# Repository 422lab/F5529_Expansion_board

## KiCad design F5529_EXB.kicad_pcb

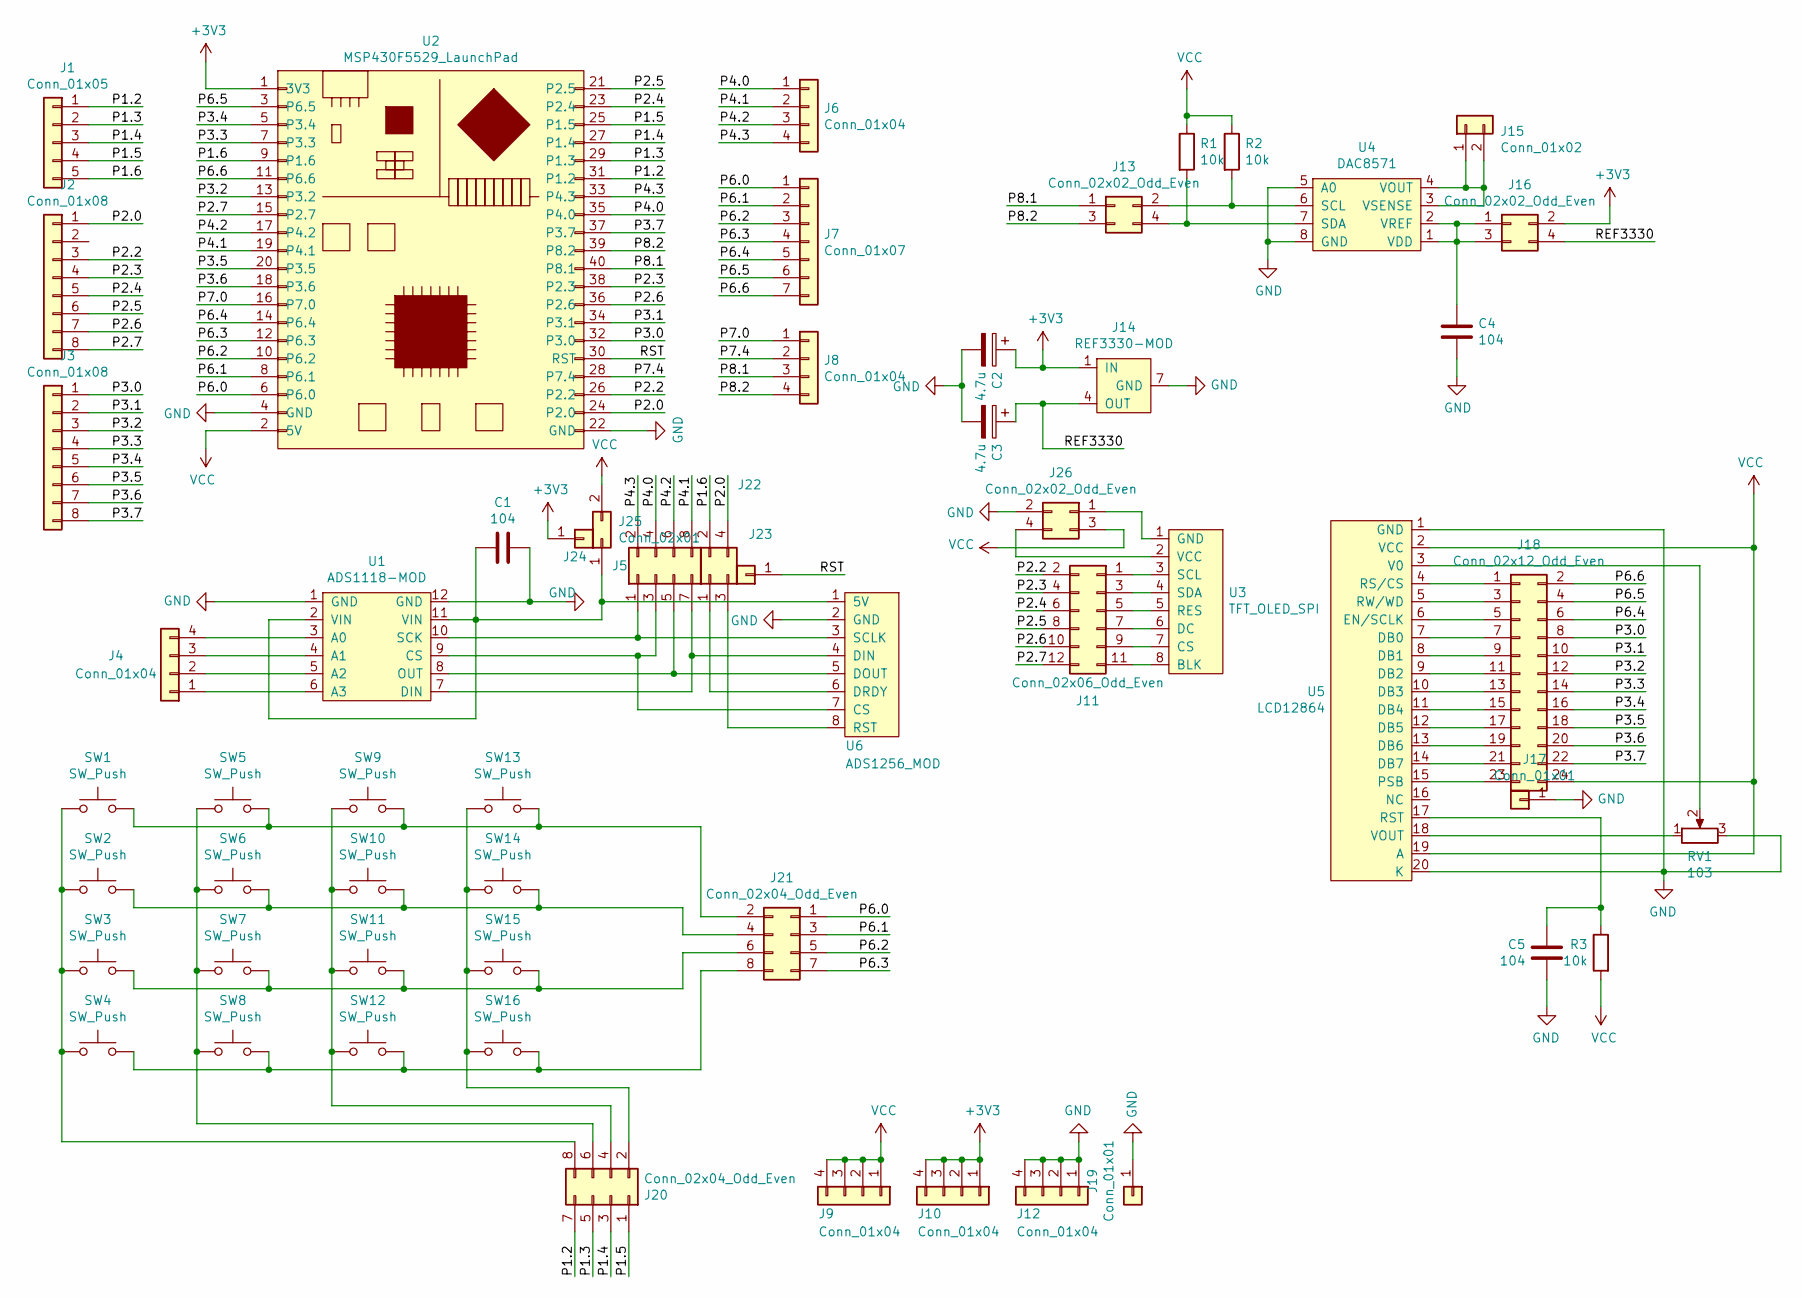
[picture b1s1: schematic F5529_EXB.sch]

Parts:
C1, C4, C5: 104; C_Disc_D3.0mm_W1.6mm_P2.50mm
C2, C3: 4.7u; CP_Radial_D5.0mm_P2.50mm
J1: Conn_01x05; PinHeader_1x05_P2.54mm_Vertical
J2, J3: Conn_01x08; PinHeader_1x08_P2.54mm_Vertical
J4, J6, J8, J9, J10, J12: Conn_01x04; PinHeader_1x04_P2.54mm_Vertical
J5, J20, J21: Conn_02x04_Odd_Even; PinHeader_2x04_P2.54mm_Vertical
J7: Conn_01x07; PinHeader_1x07_P2.54mm_Vertical
J11: Conn_02x06_Odd_Even; PinHeader_2x06_P2.54mm_Vertical
J13, J16, J22, J26: Conn_02x02_Odd_Even; PinHeader_2x02_P2.54mm_Vertical
J14: REF3330-MOD; DIP-8_W7.62mm
J15: Conn_01x02; PinHeader_1x02_P2.54mm_Vertical
J17, J23, J24: Conn_01x01; PinHeader_1x01_P2.54mm_Vertical
J18: Conn_02x12_Odd_Even; PinHeader_2x12_P2.54mm_Vertical
J19: Conn_01x01; TestPoint_Loop_D2.50mm_Drill1.85mm
J25: Conn_02x01; PinHeader_2x01_P2.54mm_Vertical
R1, R2, R3: 10k; R_Axial_DIN0207_L6.3mm_D2.5mm_P7.62mm_Horizontal
RV1: 103; Potentiometer_Bourns_3296W_Vertical
SW1, SW2, SW3, SW4, SW5, SW6, SW7, SW8, SW9, SW10, SW11, SW12, SW13, SW14, SW15, SW16: SW_Push; SW_PUSH_6mm
U1: ADS1118-MOD; ADS1118_MOD
U2: MSP430F5529_LaunchPad
U3: TFT_OLED_SPI; ZJY_1_54_SPI_ST7789
U4: DAC8571; DIP-8_W7.62mm
U5: LCD12864
U6: ADS1256_MOD; PinSocket_1x08_P2.54mm_Vertical

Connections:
+3V3: C2.1, J10.1, J10.2, J10.3, J10.4, J14.1 (IN), J16.2, J24.1, U2.1 (3V3)
/P1.2: J1.1, J20.7, U2.31 (P1.2)
/P1.3: J1.2, J20.5, U2.29 (P1.3)
/P1.4: J1.3, J20.3, U2.27 (P1.4)
/P1.5: J1.4, J20.1, U2.25 (P1.5)
/P1.6: J1.5, J22.2, U2.9 (P1.6)
/P2.0: J2.1, J22.4, U2.24 (P2.0)
/P2.2: J2.3, J11.2, U2.26 (P2.2)
/P2.3: J2.4, J11.4, U2.38 (P2.3)
/P2.4: J2.5, J11.6, U2.23 (P2.4)
/P2.5: J2.6, J11.8, U2.21 (P2.5)
/P2.6: J2.7, J11.10, U2.36 (P2.6)
/P2.7: J2.8, J11.12, U2.15 (P2.7)
/P3.0: J3.1, J18.8, U2.32 (P3.0)
/P3.1: J3.2, J18.10, U2.34 (P3.1)
/P3.2: J3.3, J18.12, U2.13 (P3.2)
/P3.3: J3.4, J18.14, U2.7 (P3.3)
/P3.4: J3.5, J18.16, U2.5 (P3.4)
/P3.5: J3.6, J18.18, U2.20 (P3.5)
/P3.6: J3.7, J18.20, U2.18 (P3.6)
/P3.7: J3.8, J18.22, U2.37 (P3.7)
/P4.0: J5.4, J6.1, U2.35 (P4.0)
/P4.1: J5.8, J6.2, U2.19 (P4.1)
/P4.2: J5.6, J6.3, U2.17 (P4.2)
/P4.3: J5.2, J6.4, U2.33 (P4.3)
/P6.0: J7.1, J21.1, U2.6 (P6.0)
/P6.1: J7.2, J21.3, U2.8 (P6.1)
/P6.2: J7.3, J21.5, U2.10 (P6.2)
/P6.3: J7.4, J21.7, U2.12 (P6.3)
/P6.4: J7.5, J18.6, U2.14 (P6.4)
/P6.5: J7.6, J18.4, U2.3 (P6.5)
/P6.6: J7.7, J18.2, U2.11 (P6.6)
/P7.0: J8.1, U2.16 (P7.0)
/P7.4: J8.2, U2.28 (P7.4)
/P8.1: J8.3, J13.1, U2.40 (P8.1)
/P8.2: J8.4, J13.3, U2.39 (P8.2)
/REF3330: C3.1, J14.4 (OUT), J16.4
/RST: J23.1, U2.30 (RST)
GND: C1.1, C2.2, C3.2, C4.2, C5.2, J12.1, J12.2, J12.3, J12.4, J14.7 (GND), J17.1, J19.1, J26.2, RV1.3, U1.1 (GND), U1.12 (GND), U2.4 (GND), U2.22 (GND), U4.5 (A0), U4.8 (GND), U5.1 (GND), U5.20 (K), U6.2 (GND)
unnamed: C1.2, J25.1, U1.2 (VIN), U1.11 (VIN), U6.1 (5V)
unnamed: C4.1, J16.1, J16.3, U4.1 (VDD), U4.2 (VREF)
unnamed: C5.1, R3.1, U5.17 (RST)
unnamed: J4.1, U1.6 (A3)
unnamed: J4.2, U1.5 (A2)
unnamed: J4.3, U1.4 (A1)
unnamed: J4.4, U1.3 (A0)
unnamed: J5.1, U1.10 (SCK), U6.3 (SCLK)
unnamed: J5.3, U1.9 (CS), U6.7 (CS)
unnamed: J5.5, U1.8 (OUT), U6.5 (DOUT)
unnamed: J5.7, U1.7 (DIN), U6.4 (DIN)
unnamed: J11.1, U3.3 (SCL)
unnamed: J11.3, U3.4 (SDA)
unnamed: J11.5, U3.5 (RES)
unnamed: J11.7, U3.6 (DC)
unnamed: J11.9, U3.7 (CS)
unnamed: J11.11, U3.8 (BLK)
unnamed: J13.2, R2.2, U4.6 (SCL)
unnamed: J13.4, R1.2, U4.7 (SDA)
unnamed: J15.1, J15.2, U4.3 (VSENSE), U4.4 (VOUT)
unnamed: J18.1, U5.4 (RS/CS)
unnamed: J18.3, U5.5 (RW/WD)
unnamed: J18.5, U5.6 (EN/SCLK)
unnamed: J18.7, U5.7 (DB0)
unnamed: J18.9, U5.8 (DB1)
unnamed: J18.11, U5.9 (DB2)
unnamed: J18.13, U5.10 (DB3)
unnamed: J18.15, U5.11 (DB4)
unnamed: J18.17, U5.12 (DB5)
unnamed: J18.19, U5.13 (DB6)
unnamed: J18.21, U5.14 (DB7)
unnamed: J18.23, U5.15 (PSB)
unnamed: J20.2, SW13.1, SW14.1, SW15.1, SW16.1
unnamed: J20.4, SW9.1, SW10.1, SW11.1, SW12.1
unnamed: J20.6, SW5.1, SW6.1, SW7.1, SW8.1
unnamed: J20.8, SW1.1, SW2.1, SW3.1, SW4.1
unnamed: J21.2, SW1.2, SW5.2, SW9.2, SW13.2
unnamed: J21.4, SW2.2, SW6.2, SW10.2, SW14.2
unnamed: J21.6, SW3.2, SW7.2, SW11.2, SW15.2
unnamed: J21.8, SW4.2, SW8.2, SW12.2, SW16.2
unnamed: J22.1, U6.6 (DRDY)
unnamed: J22.3, U6.8 (RST)
unnamed: J26.1, U3.1 (GND)
unnamed: J26.4, U3.2 (VCC)
unnamed: RV1.1, U5.18 (VOUT)
unnamed: RV1.2, U5.3 (V0)
VCC: J9.1, J9.2, J9.3, J9.4, J18.24, J25.2, J26.3, R1.1, R2.1, R3.2, U2.2 (5V), U5.2 (VCC), U5.19 (A)

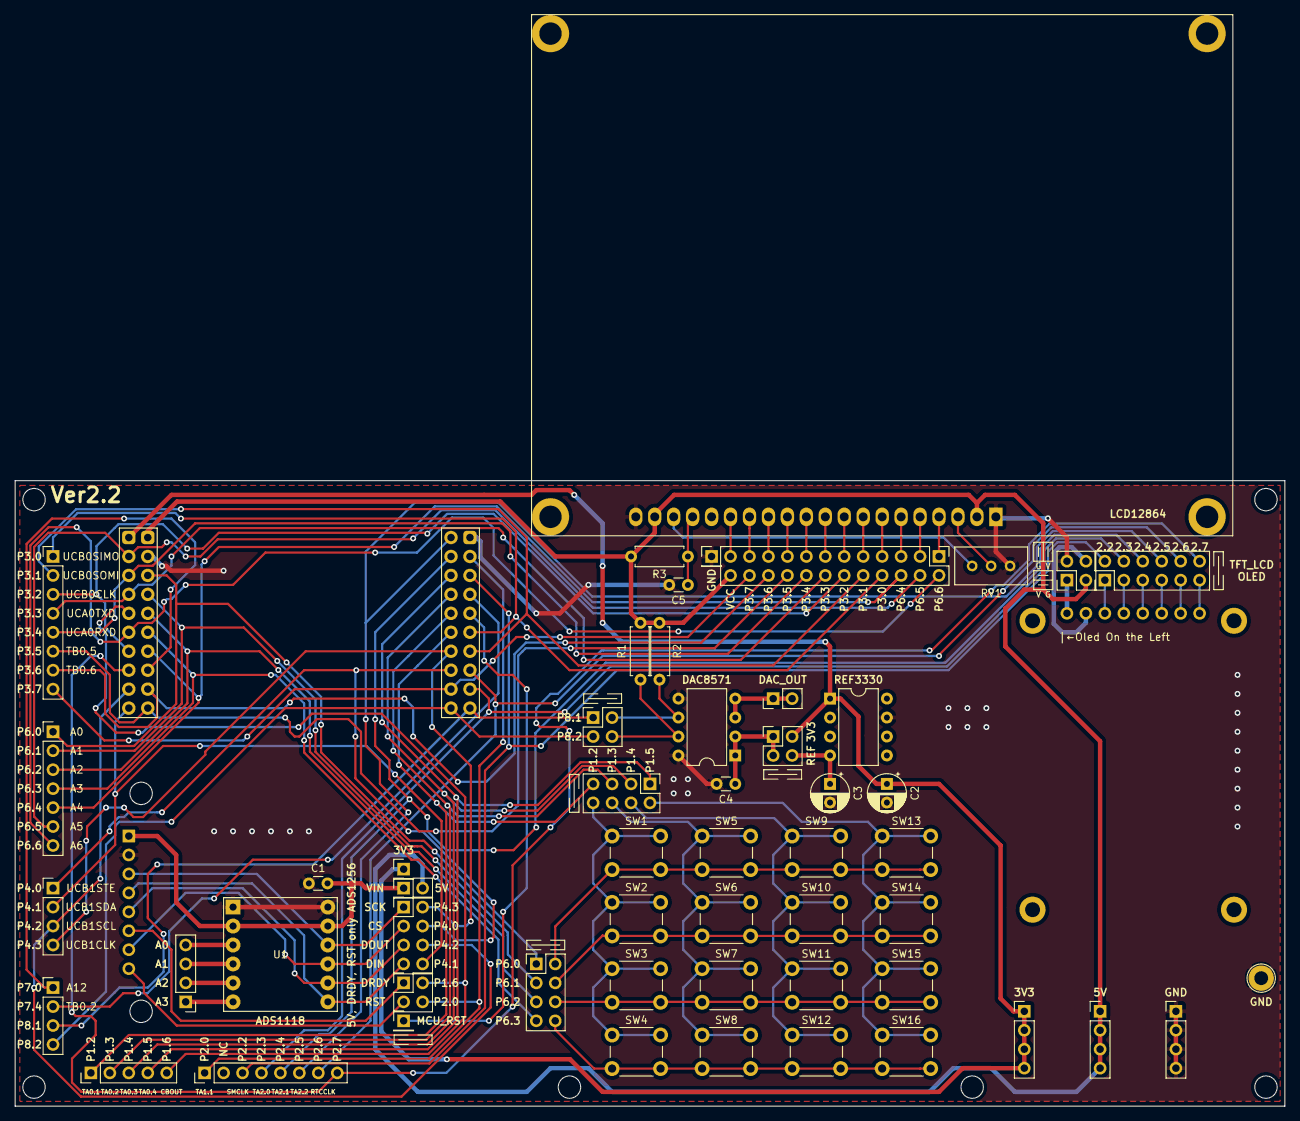
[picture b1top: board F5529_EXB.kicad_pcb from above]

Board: 2 copper layers, 170.2 x 83.8 mm, 57 parts (1 on the bottom side), 86 nets.

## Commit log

2022-03-02 仓库初始化
2022-05-16 描述修改，增加案例工程链接地址
2022-06-13 更新实物图片，更新README介绍
